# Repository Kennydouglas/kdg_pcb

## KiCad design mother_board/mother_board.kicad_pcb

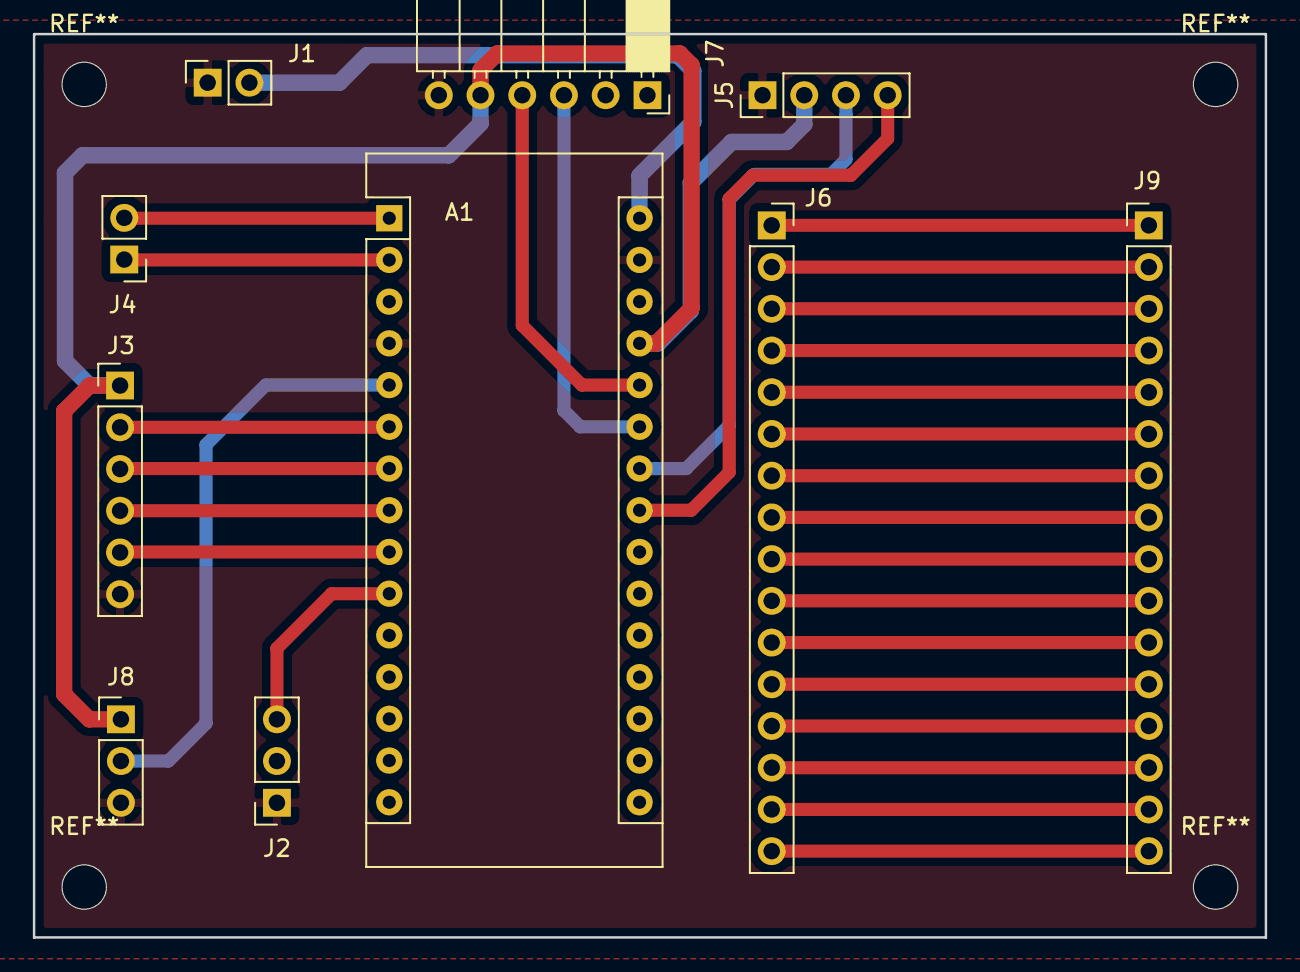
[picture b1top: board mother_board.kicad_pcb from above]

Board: 2 copper layers, 75.0 x 55.0 mm, 10 parts (0 on the bottom side), 31 nets.

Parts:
A1: Arduino_Nano_v3.x; Arduino_Nano
J1: Power Supply; PinSocket_1x02_P2.54mm_Vertical
J2: BUZZER; PinSocket_1x03_P2.54mm_Vertical
J3: RELE; PinHeader_1x06_P2.54mm_Vertical
J4: Serial; PinHeader_1x02_P2.54mm_Vertical
J5: LCD; PinHeader_1x04_P2.54mm_Vertical
J6: Conn_01x16_Female; PinSocket_1x16_P2.54mm_Vertical
J7: RTC; PinSocket_1x06_P2.54mm_Horizontal
J8: TEMPERATURE; PinHeader_1x03_P2.54mm_Vertical
J9: Conn_01x16_Male; PinHeader_1x16_P2.54mm_Vertical

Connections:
/MCU_5V: A1.27, J3.1, J5.2, J7.5, J8.1
GND: A1.4, A1.29, J1.1, J2.1, J3.6, J5.1, J7.6, J8.3
unnamed: A1.1, J4.2
unnamed: A1.2, J4.1
unnamed: A1.5, J8.2
unnamed: A1.6, J3.2
unnamed: A1.7, J3.3
unnamed: A1.8, J3.4
unnamed: A1.9, J3.5
unnamed: A1.10, J2.3
unnamed: A1.23, J5.4
unnamed: A1.24, J5.3
unnamed: A1.25, J7.3
unnamed: A1.26, J7.4
unnamed: A1.30, J1.2
unnamed: J6.1, J9.1
unnamed: J6.2, J9.2
unnamed: J6.3, J9.3
unnamed: J6.4, J9.4
unnamed: J6.5, J9.5
unnamed: J6.6, J9.6
unnamed: J6.7, J9.7
unnamed: J6.8, J9.8
unnamed: J6.9, J9.9
unnamed: J6.10, J9.10
unnamed: J6.11, J9.11
unnamed: J6.12, J9.12
unnamed: J6.13, J9.13
unnamed: J6.14, J9.14
unnamed: J6.15, J9.15
unnamed: J6.16, J9.16

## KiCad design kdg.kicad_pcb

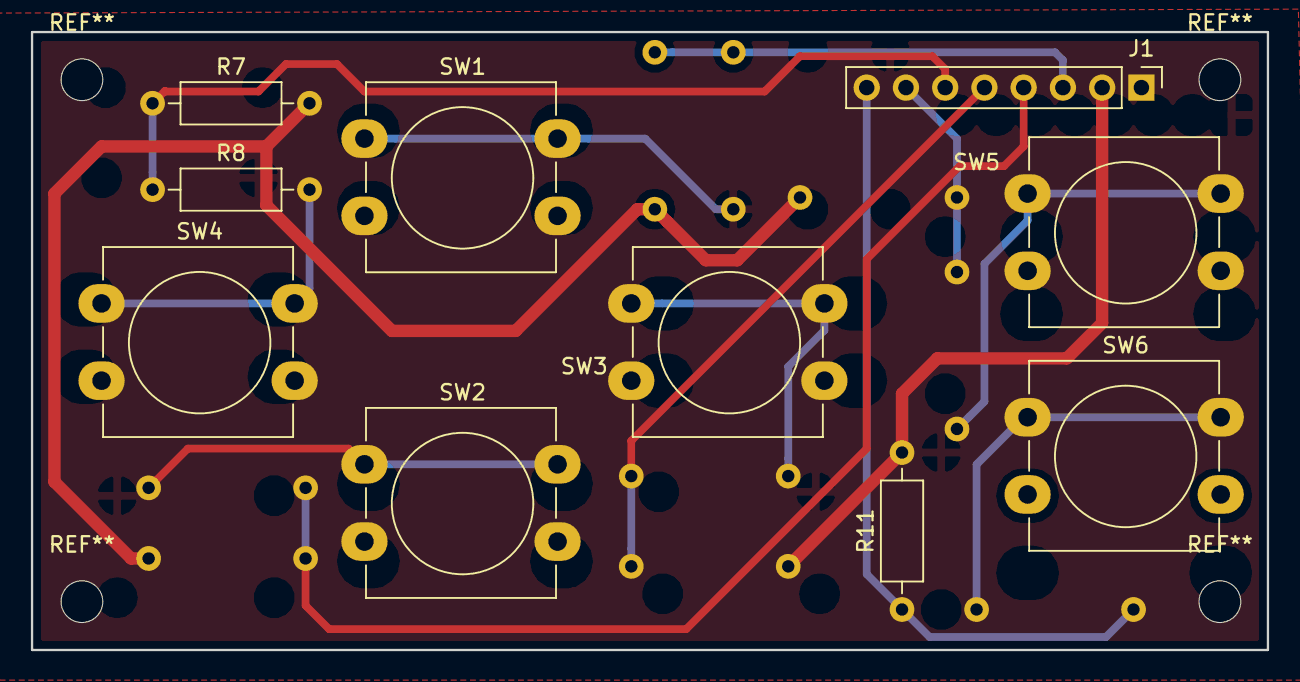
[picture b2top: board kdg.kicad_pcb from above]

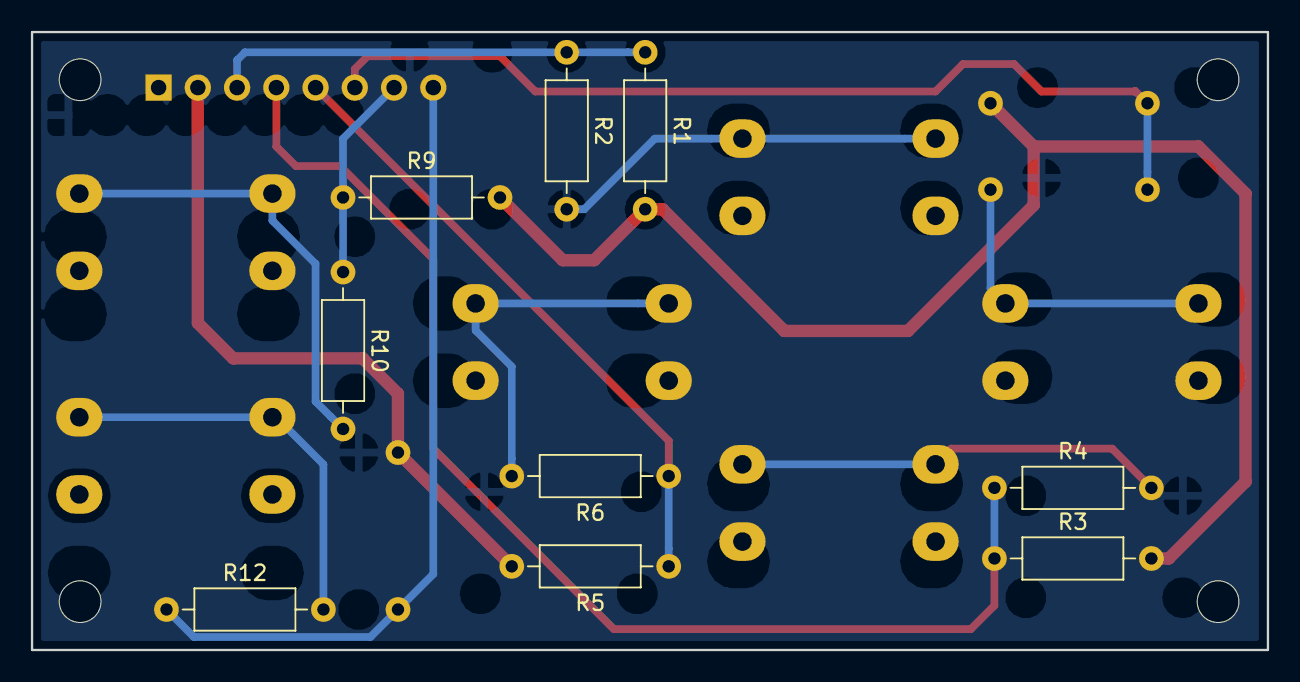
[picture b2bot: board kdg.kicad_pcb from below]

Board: 2 copper layers, 80.0 x 40.0 mm, 19 parts (9 on the bottom side), 14 nets.

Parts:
J1: Conn_01x08_Male; PinHeader_1x08_P2.54mm_Vertical
R1, R3, R5, R7, R9, R11: 100; R_Axial_DIN0207_L6.3mm_D2.5mm_P10.16mm_Horizontal
R2, R4, R6, R8, R10, R12: 1K; R_Axial_DIN0207_L6.3mm_D2.5mm_P10.16mm_Horizontal
SW1: up; SW_PUSH-12mm_Wuerth-430476085716
SW2: down; SW_PUSH-12mm_Wuerth-430476085716
SW3: right; SW_PUSH-12mm_Wuerth-430476085716
SW4: left; SW_PUSH-12mm_Wuerth-430476085716
SW5: confirm; SW_PUSH-12mm_Wuerth-430476085716
SW6: return; SW_PUSH-12mm_Wuerth-430476085716

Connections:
/VCC: J1.2, R1.2, R3.2, R5.2, R7.2, R9.2, R11.2
GND: J1.1, SW1.2, SW2.2, SW3.2, SW4.2, SW5.2, SW6.2
unnamed: J1.3, R1.1, R2.1
unnamed: J1.4, R3.1, R4.1
unnamed: J1.5, R5.1, R6.1
unnamed: J1.6, R7.1, R8.1
unnamed: J1.7, R9.1, R10.1
unnamed: J1.8, R11.1, R12.1
unnamed: R2.2, SW1.1
unnamed: R4.2, SW2.1
unnamed: R6.2, SW3.1
unnamed: R8.2, SW4.1
unnamed: R10.2, SW5.1
unnamed: R12.2, SW6.1

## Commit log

2019-03-08 Added files of panel interface
2019-03-11 Added Mother Board PCB.
